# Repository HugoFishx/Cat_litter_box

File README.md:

Cat Litter Box + - Final project of ECE473 @ Umich FA 2021
Group:
    Shiqi Yu
    Haoda Gong
    Yechen Shi
    Ruitao Long
    Tianyang Shi

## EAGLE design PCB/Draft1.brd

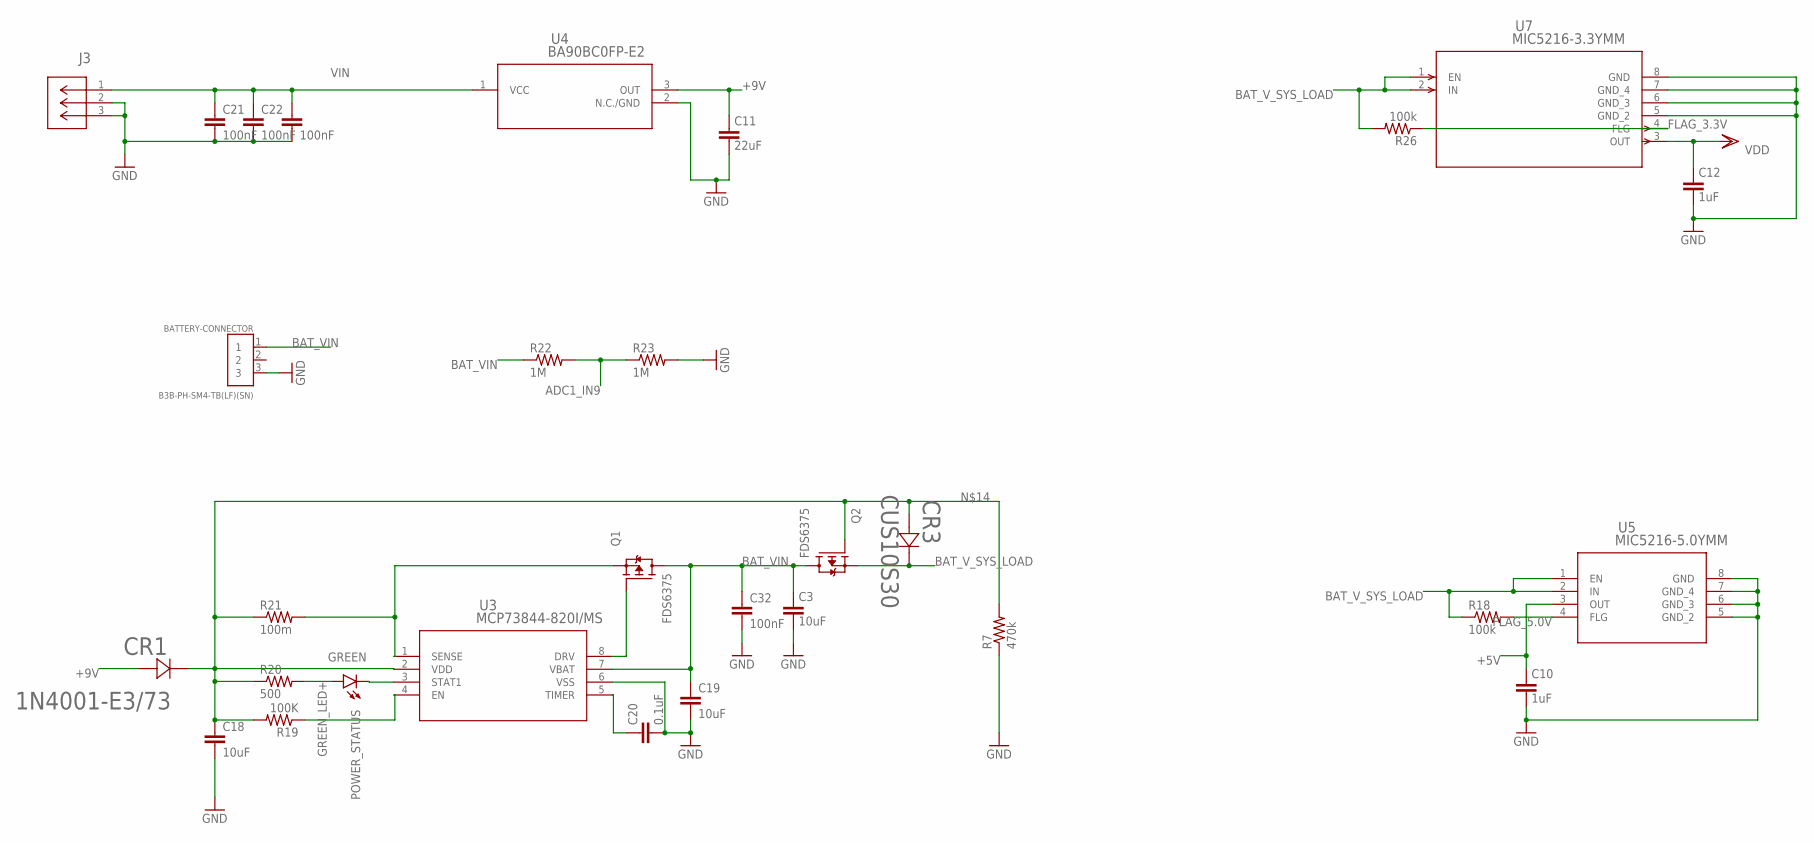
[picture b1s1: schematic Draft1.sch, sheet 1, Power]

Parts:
BATTERY-CONNECTOR: B3B-PH-SM4-TB(LF)(SN); JST_B3B-PH-SM4-TB(LF)(SN)
C3, C18, C19: 10uF; C0603
C10, C12: 1uF; C0603
C11: 22uF; C0603
C20: 0.1uF; C0603
C21, C22, C23, C32: 100nF; C0603
CR1: 1N4001-E3/73; DO-204AL_VIS
CR3: CUS10S30; USC_TOS
J3: EJ503B; CONN_EJ503B_MPD
POWER_STATUS: GREEN; 1206
Q1, Q2: FDS6375; SOIC127P600X175-8N
R7: 470k; R0603
R18, R26: 100k; R0603
R19: 100K; R0603
R20: 500; R0603
R21: 100m; R0603
R22, R23: 1M; R0603
U3: MCP73844-820I/MS; MSOP8_MC_MCH
U4: BA90BC0FP-E2; TO252-3_ROM
U5: MIC5216-5.0YMM; MSOP8_MM_MCH
U7: MIC5216-3.3YMM; MSOP-8_MM_MCL

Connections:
+5V: C10.1, U5.3 (OUT); also elsewhere on the board
+9V: C11.1, CR1.2, U4.3 (OUT)
ADC1_IN9: R22.2, R23.1; also elsewhere on the board
BAT_VIN: BATTERY-CONNECTOR.1, C3.1, C19.1, C32.1, Q1.5 (D), Q1.6 (D), Q1.7 (D), Q1.8 (D), Q2.5 (D), Q2.6 (D), Q2.7 (D), Q2.8 (D), R22.1, U3.7 (VBAT)
BAT_V_SYS_LOAD: CR3.1 (CATHODE), Q2.1 (S), Q2.2 (S), Q2.3 (S), R18.1, R26.2, U5.1 (EN), U5.2 (IN), U7.1 (EN), U7.2 (IN)
FLAG_3.3V: R26.1, U7.4 (FLG)
FLAG_5.0V: R18.2, U5.4 (FLG)
GND: BATTERY-CONNECTOR.3, C3.2, C10.2, C11.2, C12.2, C18.2, C19.2, C20.2, C21.2, C22.2, C23.2, C32.2, J3.2, J3.3, R7.1, R23.2, U3.6 (VSS), U4.2 (N.C./GND), U5.5 (GND_2), U5.6 (GND_3), U5.7 (GND_4), U5.8 (GND), U7.5 (GND_2), U7.6 (GND_3), U7.7 (GND_4), U7.8 (GND); also elsewhere on the board
GREEN_LED+: POWER_STATUS.A, R20.2
unnamed: C18.1, CR1.1, CR3.2 (ANODE), Q2.4 (G), R7.2, R19.2, R20.1, R21.1, U3.2 (VDD)
unnamed: R19.1, U3.4 (EN)
unnamed: POWER_STATUS.C, U3.3 (STAT1)
unnamed: Q1.4 (G), U3.8 (DRV)
unnamed: Q1.1 (S), Q1.2 (S), Q1.3 (S), R21.2, U3.1 (SENSE)
unnamed: C20.1, U3.5 (TIMER)
VDD: C12.1, U7.3 (OUT); also elsewhere on the board
VIN: C21.1, C22.1, C23.1, J3.1, U4.1 (VCC)

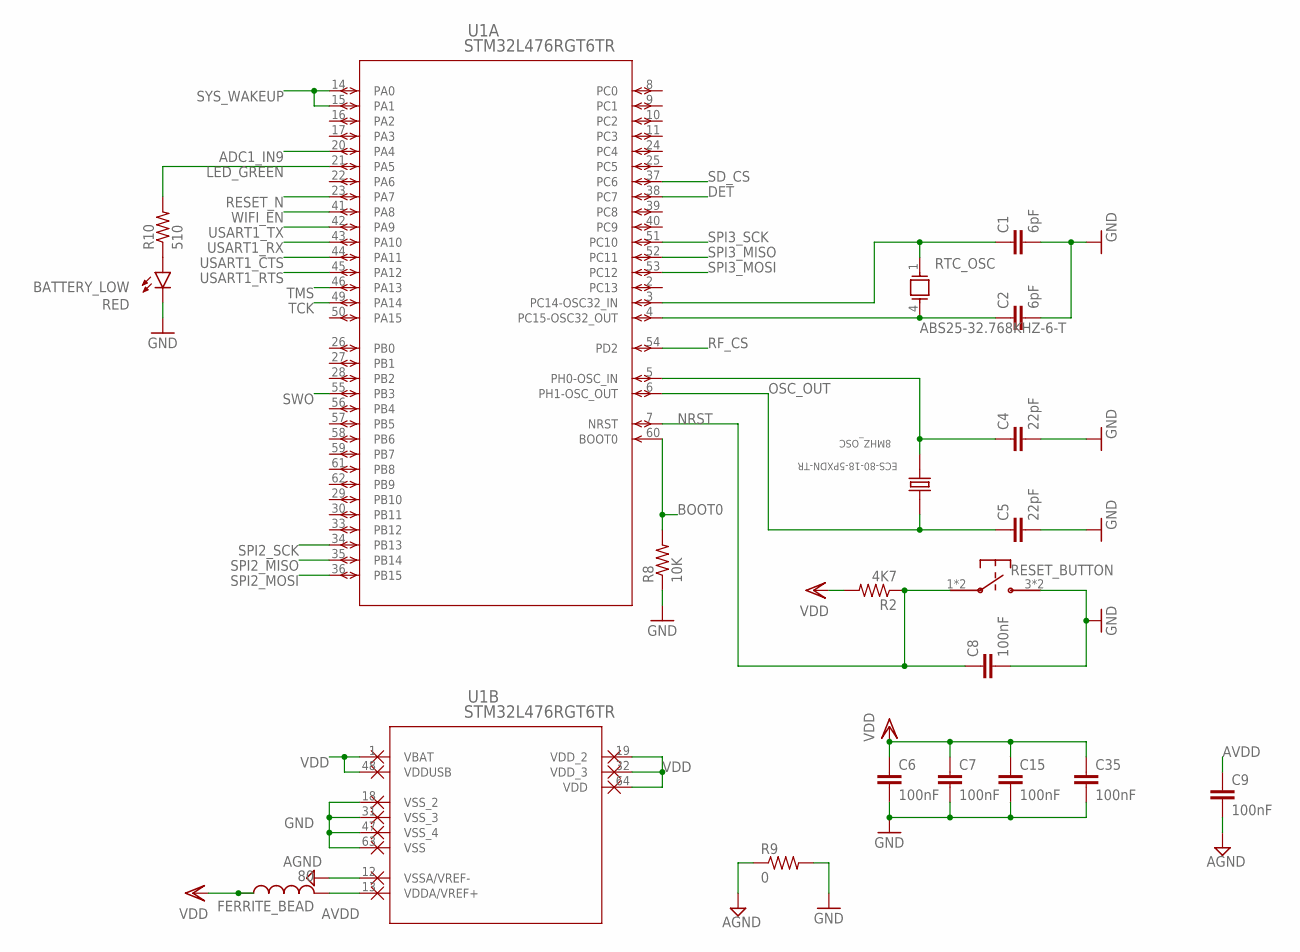
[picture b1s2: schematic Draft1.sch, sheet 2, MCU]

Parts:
8MHZ_OSC: ECS-80-18-5PXDN-TR; XTAL_ECS-80-18-5PXDN-TR
BATTERY_LOW: RED; 1206
C1, C2: 6pF; C0603
C4, C5: 22pF; C0603
C6, C7, C8, C9, C15, C35: 100nF; C0603
FERRITE_BEAD: 80; L3216C
R2: 4K7; R0603
R8: 10K; R0603
R9: 0; R0603
R10: 510; R0603
RESET_BUTTON: PTS645SM43SMTR
RTC_OSC: ABS25-32.768KHZ-6-T; XTAL_ABS25-32.768KHZ-6-T
U1: STM32L476RGT6TR; LQFP64-10X10MM

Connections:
ADC1_IN9: U1.20 (PA4); also elsewhere on the board
AGND: C9.2, R9.1, U1.12 (VSSA/VREF-)
AVDD: C9.1, FERRITE_BEAD.2, U1.13 (VDDA/VREF+)
BOOT0: R8.2, U1.60 (BOOT0)
DET: U1.38 (PC7); also elsewhere on the board
GND: BATTERY_LOW.C, C1.2, C2.2, C4.2, C5.2, C6.2, C7.2, C8.2, C15.2, C35.2, R8.1, R9.2, RESET_BUTTON.3, RESET_BUTTON.4, U1.18 (VSS_2), U1.31 (VSS_3), U1.47 (VSS_4), U1.63 (VSS); also elsewhere on the board
LED_GREEN: R10.2, U1.21 (PA5)
unnamed: BATTERY_LOW.A, R10.1
unnamed: C1.1, RTC_OSC.1, U1.3 (PC14-OSC32_IN)
unnamed: C2.1, RTC_OSC.4, U1.4 (PC15-OSC32_OUT)
NRST: C8.1, R2.1, RESET_BUTTON.1, RESET_BUTTON.2, U1.7 (NRST); also elsewhere on the board
OSC_IN: 8MHZ_OSC.2, C4.1, U1.5 (PH0-OSC_IN)
OSC_OUT: 8MHZ_OSC.1, C5.1, U1.6 (PH1-OSC_OUT); also elsewhere on the board
RESET_N: U1.23 (PA7); also elsewhere on the board
RF_CS: U1.54 (PD2); also elsewhere on the board
SD_CS: U1.37 (PC6); also elsewhere on the board
SPI2_MISO: U1.35 (PB14); also elsewhere on the board
SPI2_MOSI: U1.36 (PB15); also elsewhere on the board
SPI2_SCK: U1.34 (PB13); also elsewhere on the board
SPI3_MISO: U1.52 (PC11); also elsewhere on the board
SPI3_MOSI: U1.53 (PC12); also elsewhere on the board
SPI3_SCK: U1.51 (PC10); also elsewhere on the board
SWO: U1.55 (PB3); also elsewhere on the board
SYS_WAKEUP: U1.14 (PA0), U1.15 (PA1); also elsewhere on the board
TCK: U1.49 (PA14); also elsewhere on the board
TMS: U1.46 (PA13); also elsewhere on the board
USART1_CTS: U1.44 (PA11); also elsewhere on the board
USART1_RTS: U1.45 (PA12); also elsewhere on the board
USART1_RX: U1.43 (PA10); also elsewhere on the board
USART1_TX: U1.42 (PA9); also elsewhere on the board
VDD: C6.1, C7.1, C15.1, C35.1, FERRITE_BEAD.1, R2.2, U1.1 (VBAT), U1.19 (VDD_2), U1.32 (VDD_3), U1.48 (VDDUSB), U1.64 (VDD); also elsewhere on the board
WIFI_EN: U1.41 (PA8); also elsewhere on the board

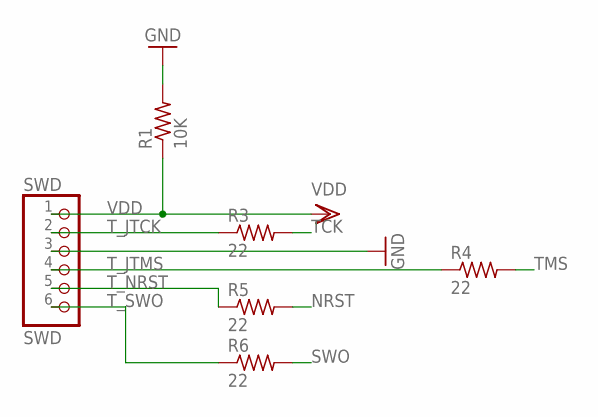
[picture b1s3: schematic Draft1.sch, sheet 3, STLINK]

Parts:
R1: 10K; R0603
R3, R4, R5, R6: 22; R0603
SWD: SWD; 1X06

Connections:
GND: R1.2, SWD.3; also elsewhere on the board
NRST: R5.2; also elsewhere on the board
SWO: R6.2; also elsewhere on the board
TCK: R3.2; also elsewhere on the board
TMS: R4.2; also elsewhere on the board
T_JTCK: R3.1, SWD.2
T_JTMS: R4.1, SWD.4
T_NRST: R5.1, SWD.5
T_SWO: R6.1, SWD.6
VDD: R1.1, SWD.1; also elsewhere on the board

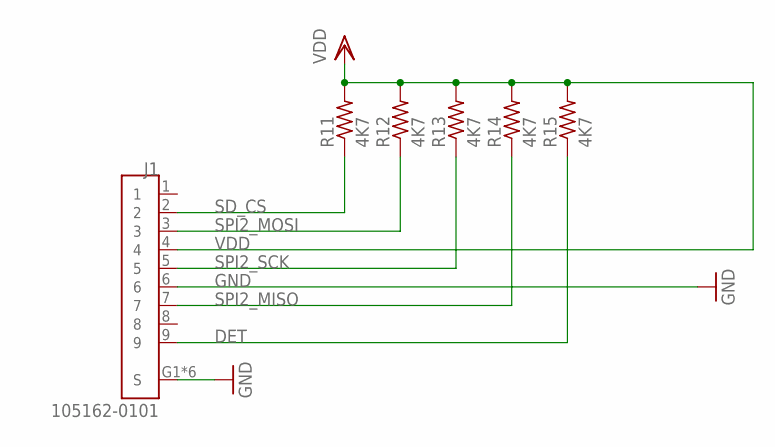
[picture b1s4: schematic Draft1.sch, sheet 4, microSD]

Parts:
J1: 105162-0101; MOLEX_105162-0101
R11, R12, R13, R14, R15: 4K7; R0603

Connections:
DET: J1.9, R15.1; also elsewhere on the board
GND: J1.6, J1.G1 (S), J1.G2 (S), J1.G3 (S), J1.G4 (S), J1.SH1 (S), J1.SH2 (S); also elsewhere on the board
SD_CS: J1.2, R11.1; also elsewhere on the board
SPI2_MISO: J1.7, R14.1; also elsewhere on the board
SPI2_MOSI: J1.3, R12.1; also elsewhere on the board
SPI2_SCK: J1.5, R13.1; also elsewhere on the board
VDD: J1.4, R11.2, R12.2, R13.2, R14.2, R15.2; also elsewhere on the board

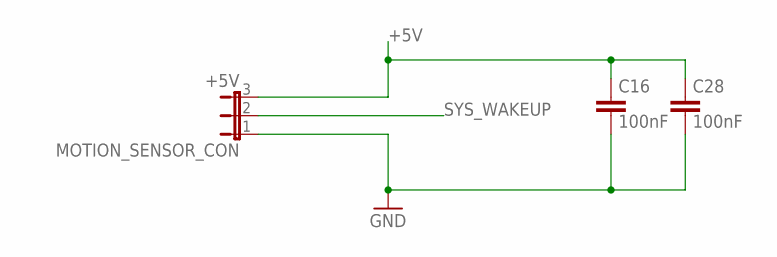
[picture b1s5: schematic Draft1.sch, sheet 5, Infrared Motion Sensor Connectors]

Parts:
C16, C28: 100nF; C0603
MOTION_SENSOR_CON: +5V; JP2

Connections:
+5V: C16.1, C28.1, MOTION_SENSOR_CON.3; also elsewhere on the board
GND: C16.2, C28.2, MOTION_SENSOR_CON.1; also elsewhere on the board
SYS_WAKEUP: MOTION_SENSOR_CON.2; also elsewhere on the board

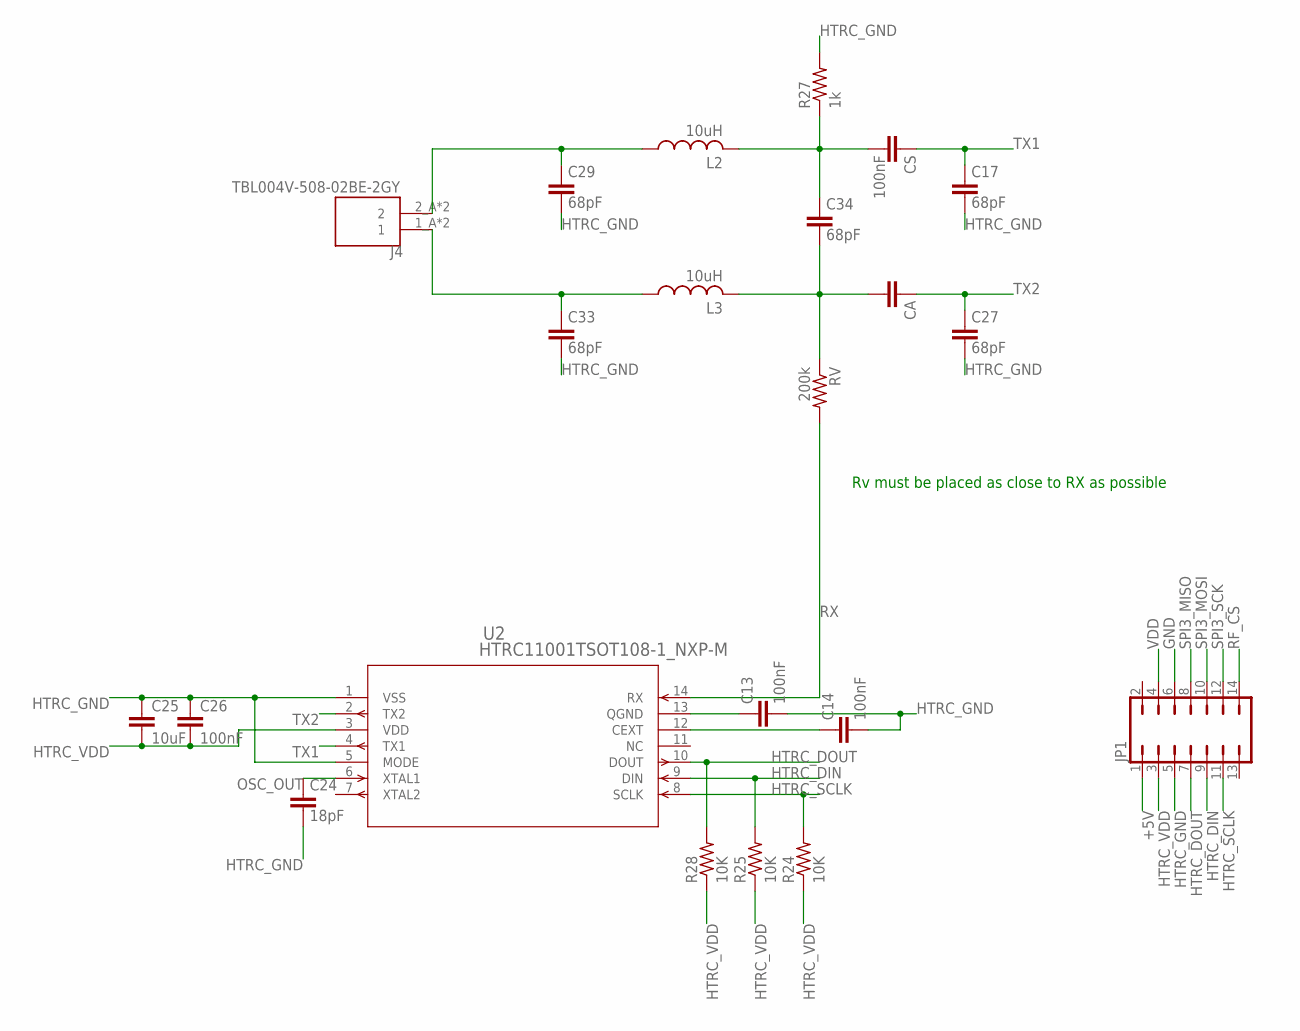
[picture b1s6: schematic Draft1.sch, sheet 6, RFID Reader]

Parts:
C13, C14, C26: 100nF; C0603
C17, C27, C29, C33, C34: 68pF; C0603
C24: 18pF; C0603
C25: 10uF; C0603
CA: C-EUC0603; C0603
CS: 100nF; C0603
J4: TBL004V-508-02BE-2GY; CUI_TBL004V-508-02BE-2GY
JP1: JP7Q
L2, L3: 10uH; L3225M
R24, R25, R28: 10K; R0603
R27: 1k; R0603
RV: 200k; R0603
U2: HTRC11001TSOT108-1_NXP-M; SOT108-1_NXP-M

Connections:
+5V: JP1.1; also elsewhere on the board
GND: JP1.6; also elsewhere on the board
HTRC_DIN: JP1.9, R25.2, U2.9 (DIN)
HTRC_DOUT: JP1.7, R28.2, U2.10 (DOUT)
HTRC_GND: C13.2, C14.2, C17.2, C24.2, C25.1, C26.1, C27.2, C29.2, C33.2, JP1.5, R27.2, U2.1 (VSS), U2.5 (MODE)
HTRC_SCLK: JP1.11, R24.2, U2.8 (SCLK)
HTRC_VDD: C25.2, C26.2, JP1.3, R24.1, R25.1, R28.1, U2.3 (VDD)
unnamed: C33.1, J4.1_A (1), J4.1_B (1), L3.1
unnamed: C29.1, J4.2_A (2), J4.2_B (2), L2.1
unnamed: C34.1, CS.2, L2.2, R27.1
unnamed: C13.1, U2.13 (QGND)
unnamed: C34.2, CA.2, L3.2, RV.1
unnamed: C14.1, U2.12 (CEXT)
OSC_OUT: C24.1, U2.6 (XTAL1); also elsewhere on the board
RF_CS: JP1.14; also elsewhere on the board
RX: RV.2, U2.14 (RX)
SPI3_MISO: JP1.8; also elsewhere on the board
SPI3_MOSI: JP1.10; also elsewhere on the board
SPI3_SCK: JP1.12; also elsewhere on the board
TX1: C17.1, CS.1, U2.4 (TX1)
TX2: C27.1, CA.1, U2.2 (TX2)
VDD: JP1.4; also elsewhere on the board

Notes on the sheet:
Rv must be placed as close to RX as possible

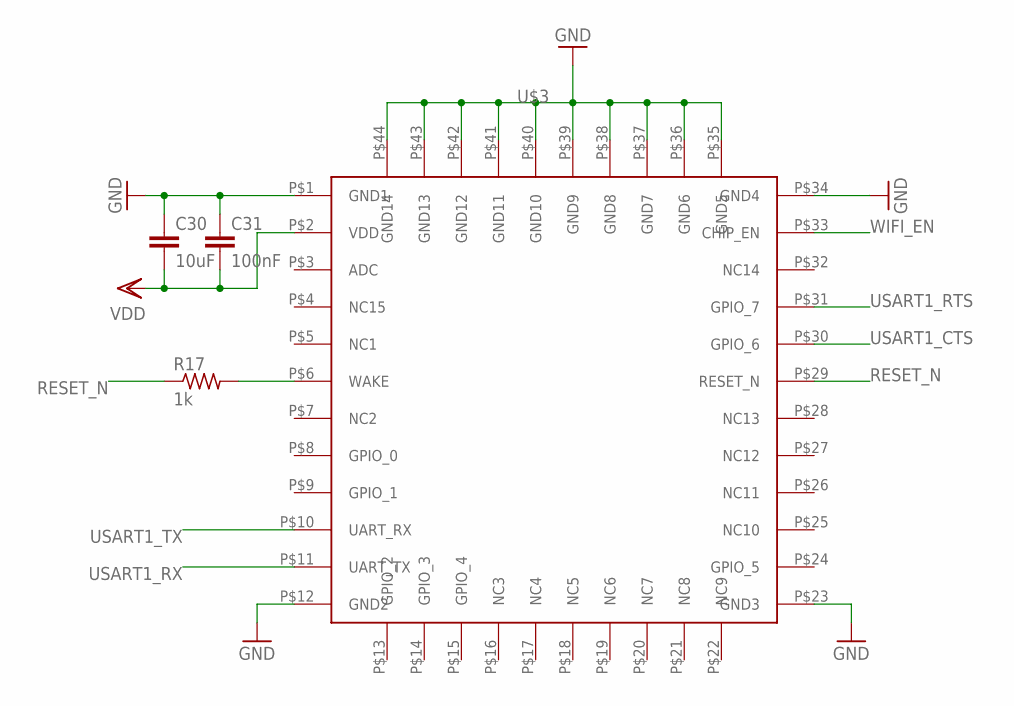
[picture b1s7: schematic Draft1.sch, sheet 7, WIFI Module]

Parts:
C30: 10uF; C0603
C31: 100nF; C0603
R17: 1k; R0603
U$3: AMW037-2.2.14R

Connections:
GND: C30.1, C31.1, U$3.P$1 (GND1), U$3.P$12 (GND2), U$3.P$23 (GND3), U$3.P$34 (GND4), U$3.P$35 (GND5), U$3.P$36 (GND6), U$3.P$37 (GND7), U$3.P$38 (GND8), U$3.P$39 (GND9), U$3.P$40 (GND10), U$3.P$41 (GND11), U$3.P$42 (GND12), U$3.P$43 (GND13), U$3.P$44 (GND14); also elsewhere on the board
unnamed: R17.2, U$3.P$6 (WAKE)
RESET_N: R17.1, U$3.P$29 (RESET_N); also elsewhere on the board
USART1_CTS: U$3.P$30 (GPIO_6); also elsewhere on the board
USART1_RTS: U$3.P$31 (GPIO_7); also elsewhere on the board
USART1_RX: U$3.P$11 (UART_TX); also elsewhere on the board
USART1_TX: U$3.P$10 (UART_RX); also elsewhere on the board
VDD: C30.2, C31.2, U$3.P$2 (VDD); also elsewhere on the board
WIFI_EN: U$3.P$33 (CHIP_EN); also elsewhere on the board

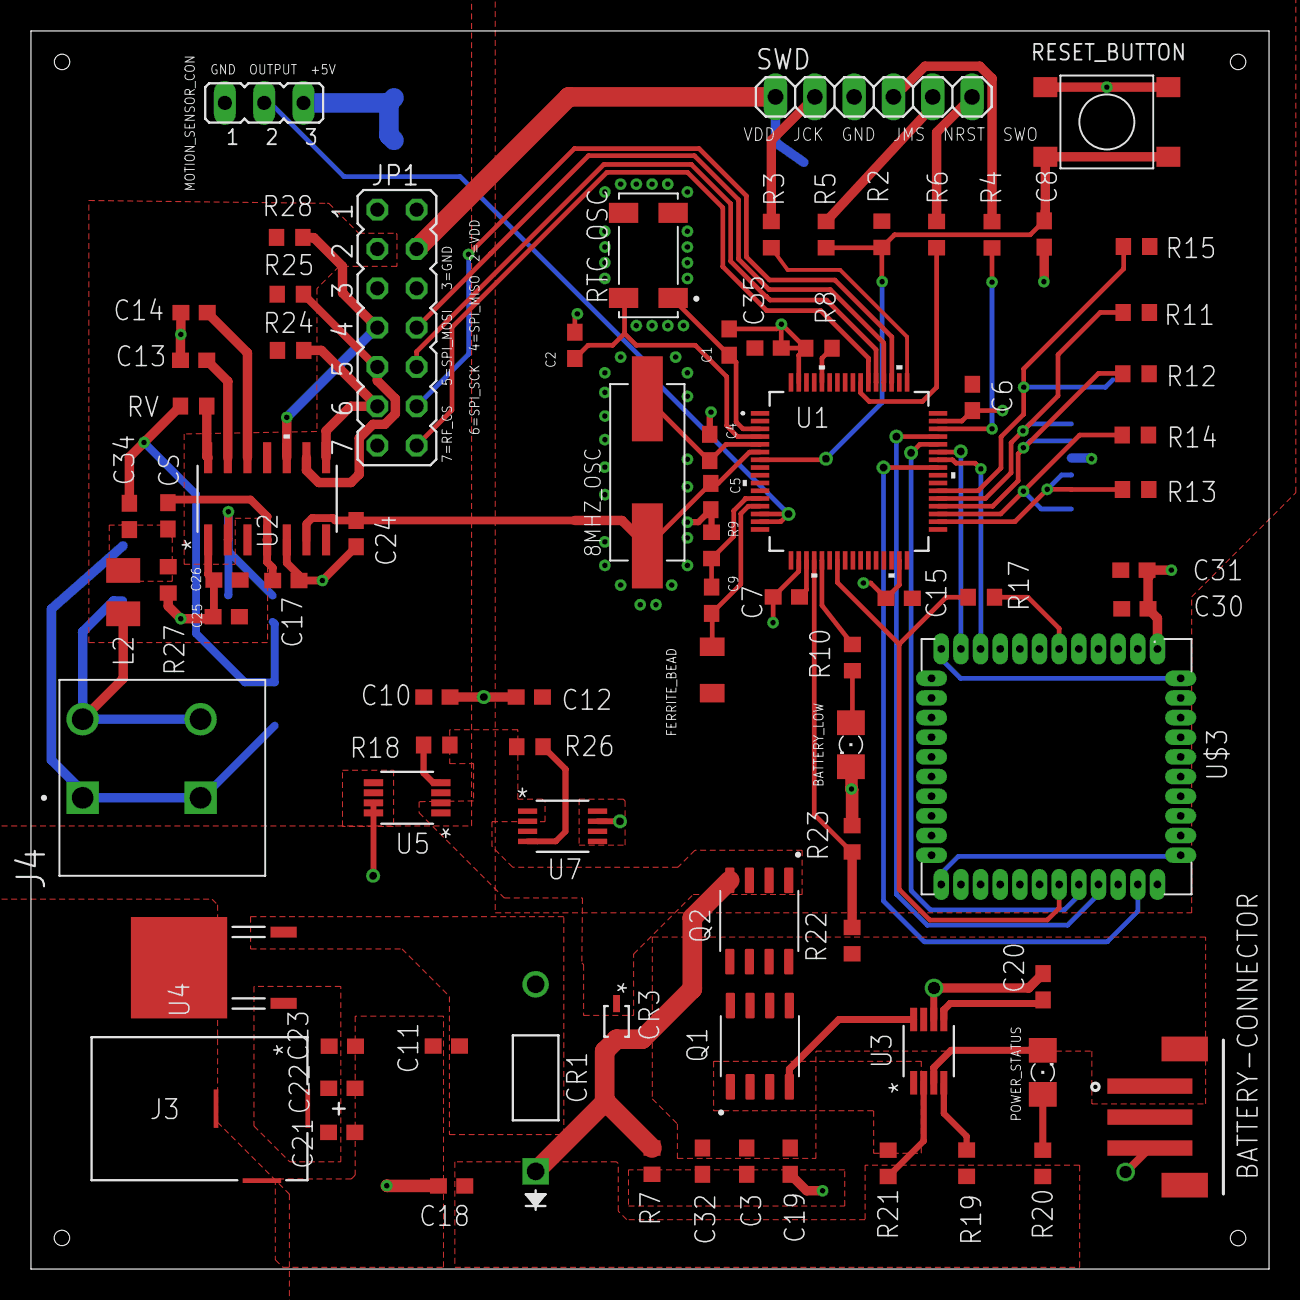
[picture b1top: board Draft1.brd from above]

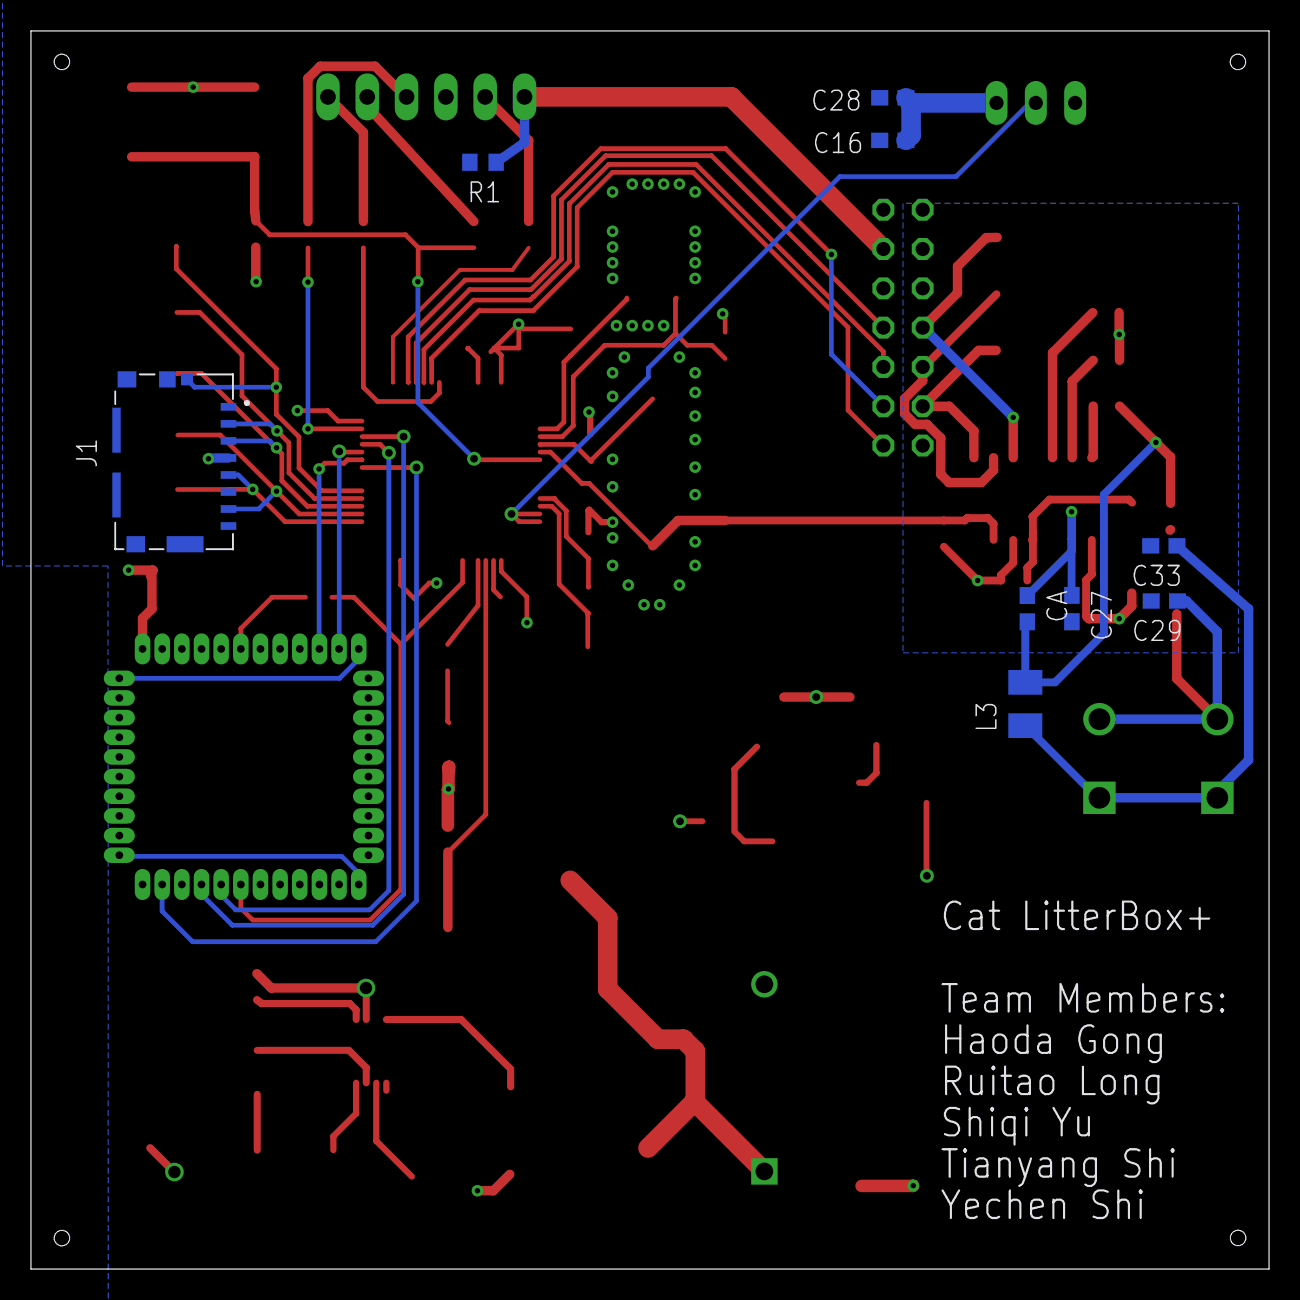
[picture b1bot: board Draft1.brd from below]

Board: 2 copper layers, 80.0 x 80.0 mm, 91 parts (9 on the bottom side), 65 nets.

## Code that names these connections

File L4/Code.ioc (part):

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Mcu.Name=STM32L476R(C-E-G)Tx
Mcu.Package=LQFP64
Mcu.UserName=STM32L476RGTx
PA0.Mode=SYS_WakeUp0
PA0.Signal=SYS_WKUP1
PA1.GPIOParameters=GPIO_Label,GPIO_ModeDefaultEXTI
PA1.GPIO_Label=MOTION_SENSOR_PIN
PA1.GPIO_ModeDefaultEXTI=GPIO_MODE_IT_RISING_FALLING
PA1.Signal=GPXTI1
PA10.Mode=Asynchronous
PA10.Signal=USART1_RX
PA13\ (JTMS-SWDIO).GPIOParameters=GPIO_Label
PA13\ (JTMS-SWDIO).GPIO_Label=TMS
PA13\ (JTMS-SWDIO).Mode=Serial_Wire
PA13\ (JTMS-SWDIO).Signal=SYS_JTMS-SWDIO
PA14\ (JTCK-SWCLK).GPIOParameters=GPIO_Label
PA14\ (JTCK-SWCLK).GPIO_Label=TCK
PA14\ (JTCK-SWCLK).Mode=Serial_Wire
PA14\ (JTCK-SWCLK).Signal=SYS_JTCK-SWCLK
PA2.Mode=Asynchronous
PA2.Signal=USART2_TX
PA3.GPIOParameters=GPIO_Speed,GPIO_PuPd,GPIO_Label,GPIO_Mode
PA3.GPIO_Label=USART_RX
PA3.GPIO_Mode=GPIO_MODE_AF_PP
PA3.GPIO_PuPd=GPIO_NOPULL
PA3.GPIO_Speed=GPIO_SPEED_FREQ_VERY_HIGH
PA3.Mode=Asynchronous
PA3.Signal=USART2_RX
PA4.Signal=SharedAnalog_PA4
PA5.GPIOParameters=GPIO_Label
PA5.GPIO_Label=BATTERY_LOW_LED
PA5.Signal=GPIO_Output
PA7.GPIOParameters=GPIO_Label
PA7.GPIO_Label=WIFI_RESET
PA7.Signal=GPIO_Output
PA8.GPIOParameters=GPIO_Label
PA8.GPIO_Label=WIFI_EN
PA8.Signal=GPIO_Output
PA9.Mode=Asynchronous
PA9.Signal=USART1_TX
PB13.Mode=Full_Duplex_Master
PB13.Signal=SPI2_SCK
PB14.Mode=Full_Duplex_Master
PB14.Signal=SPI2_MISO
PB15.Mode=Full_Duplex_Master
PB15.Signal=SPI2_MOSI
PB3\ (JTDO-TRACESWO).GPIOParameters=GPIO_Label
PB3\ (JTDO-TRACESWO).GPIO_Label=SWO
PB3\ (JTDO-TRACESWO).Signal=SYS_JTDO-SWO
PC10.Mode=Full_Duplex_Master
PC10.Signal=SPI3_SCK
PC11.Mode=Full_Duplex_Master
PC11.Signal=SPI3_MISO
PC12.Mode=Full_Duplex_Master
PC12.Signal=SPI3_MOSI
PC13.GPIOParameters=GPIO_PuPd,GPIO_Label,GPIO_ModeDefaultEXTI
PC13.GPIO_Label=B1 [Blue PushButton]
PC13.GPIO_ModeDefaultEXTI=GPIO_MODE_IT_FALLING
PC13.GPIO_PuPd=GPIO_NOPULL
PC13.Signal=GPXTI13
PC14-OSC32_IN\ (PC14).Signal=RCC_OSC32_IN
PC15-OSC32_OUT\ (PC15).Signal=RCC_OSC32_OUT
PC4.Mode=Asynchronous
PC4.Signal=USART3_TX
PC5.Mode=Asynchronous
PC5.Signal=USART3_RX
PC6.GPIOParameters=GPIO_Label
PC6.GPIO_Label=MICROSD_CS
PC6.Signal=GPIO_Output
PC7.GPIOParameters=GPIO_Label
PC7.GPIO_Label=MICROSD_DET
PC7.Signal=GPIO_Input
PD2.GPIOParameters=GPIO_Label
PD2.GPIO_Label=RFID_CS
PD2.Signal=GPIO_Output
PH0-OSC_IN\ (PH0).Mode=HSE-External-Oscillator
PH0-OSC_IN\ (PH0).Signal=RCC_OSC_IN
PH1-OSC_OUT\ (PH1).Mode=HSE-External-Oscillator
PH1-OSC_OUT\ (PH1).Signal=RCC_OSC_OUT
RCC.HSE_VALUE=8000000
RCC.SYSCLKFreq_VALUE=10000000
RCC.SYSCLKSource=RCC_SYSCLKSOURCE_PLLCLK
board=NUCLEO-L476RG
boardIOC=true

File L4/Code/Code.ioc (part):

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Mcu.Name=STM32L476R(C-E-G)Tx
Mcu.Package=LQFP64
Mcu.UserName=STM32L476RGTx
PA0.GPIOParameters=GPIO_Label
PA0.GPIO_Label=MS
PA0.Signal=GPXTI0
PA10.Mode=Asynchronous
PA10.Signal=USART1_RX
PA11.Mode=CTS_RTS
PA11.Signal=USART1_CTS
PA12.Mode=CTS_RTS
PA12.Signal=USART1_RTS
PA13\ (JTMS-SWDIO).GPIOParameters=GPIO_Label
PA13\ (JTMS-SWDIO).GPIO_Label=TMS
PA13\ (JTMS-SWDIO).Mode=Serial_Wire
PA13\ (JTMS-SWDIO).Signal=SYS_JTMS-SWDIO
PA14\ (JTCK-SWCLK).GPIOParameters=GPIO_Label
PA14\ (JTCK-SWCLK).GPIO_Label=TCK
PA14\ (JTCK-SWCLK).Mode=Serial_Wire
PA14\ (JTCK-SWCLK).Signal=SYS_JTCK-SWCLK
PA2.GPIOParameters=GPIO_Speed,GPIO_PuPd,GPIO_Label,GPIO_Mode
PA2.GPIO_Label=USART_TX
PA2.GPIO_Mode=GPIO_MODE_AF_PP
PA2.GPIO_PuPd=GPIO_NOPULL
PA2.GPIO_Speed=GPIO_SPEED_FREQ_VERY_HIGH
PA2.Mode=Asynchronous
PA2.Signal=USART2_TX
PA3.GPIOParameters=GPIO_Speed,GPIO_PuPd,GPIO_Label,GPIO_Mode
PA3.GPIO_Label=USART_RX
PA3.GPIO_Mode=GPIO_MODE_AF_PP
PA3.GPIO_PuPd=GPIO_NOPULL
PA3.GPIO_Speed=GPIO_SPEED_FREQ_VERY_HIGH
PA3.Mode=Asynchronous
PA3.Signal=USART2_RX
PA5.GPIOParameters=GPIO_Label
PA5.GPIO_Label=BATTERY_LOW_LED
PA5.Signal=GPIO_Output
PA8.GPIOParameters=GPIO_Label
PA8.GPIO_Label=WIFI_EN
PA8.Signal=GPIO_Output
PA9.Mode=Asynchronous
PA9.Signal=USART1_TX
PB10.Mode=Full_Duplex_Master
PB10.Signal=SPI2_SCK
PB13.GPIOParameters=GPIO_Label
PB13.GPIO_Label=CS_SD
PB13.Signal=GPIO_Output
PB14.GPIOParameters=GPIO_Label
PB14.GPIO_Label=DET
PB14.Signal=GPIO_Input
PB3\ (JTDO-TRACESWO).GPIOParameters=GPIO_Label
PB3\ (JTDO-TRACESWO).GPIO_Label=SWO
PB3\ (JTDO-TRACESWO).Signal=SYS_JTDO-SWO
PC0.Signal=ADCx_IN1
PC10.Mode=Full_Duplex_Master
PC10.Signal=SPI3_SCK
PC11.Mode=Full_Duplex_Master
PC11.Signal=SPI3_MISO
PC12.Mode=Full_Duplex_Master
PC12.Signal=SPI3_MOSI
PC13.GPIOParameters=GPIO_PuPd,GPIO_Label,GPIO_ModeDefaultEXTI
PC13.GPIO_Label=B1 [Blue PushButton]
PC13.GPIO_ModeDefaultEXTI=GPIO_MODE_IT_FALLING
PC13.GPIO_PuPd=GPIO_NOPULL
PC13.Signal=GPXTI13
PC14-OSC32_IN\ (PC14).Mode=LSE-External-Oscillator
PC14-OSC32_IN\ (PC14).Signal=RCC_OSC32_IN
PC15-OSC32_OUT\ (PC15).Mode=LSE-External-Oscillator
PC15-OSC32_OUT\ (PC15).Signal=RCC_OSC32_OUT
PC2.Mode=Full_Duplex_Master
PC2.Signal=SPI2_MISO
PC3.Mode=Full_Duplex_Master
PC3.Signal=SPI2_MOSI
PH0-OSC_IN\ (PH0).Mode=HSE-External-Oscillator
PH0-OSC_IN\ (PH0).Signal=RCC_OSC_IN
PH1-OSC_OUT\ (PH1).Mode=HSE-External-Oscillator
PH1-OSC_OUT\ (PH1).Signal=RCC_OSC_OUT
RCC.HSE_VALUE=8000000
RCC.SYSCLKFreq_VALUE=80000000
RCC.SYSCLKSource=RCC_SYSCLKSOURCE_PLLCLK
board=NUCLEO-L476RG
boardIOC=true

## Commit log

2021-10-07 Setup
2021-10-11 Arduino prototype framework
2021-10-12 Arduino motion sensor handler
2021-10-12 resource doc
2021-10-12 wrap up motion sensor
2021-10-12 ESP32 setup & serial communication & UDP
2021-10-12 weird bug in UDP
    UDP not correct when there are more than 11 bytes in the packet
2021-10-13 SD card integrated & cmd via serial
2021-10-13 trivial
2021-10-14 Arduino Low Power
2021-10-14 125kHz low freq RFID, able to extract tags
2021-10-14 Web Server & UDP fixed & buglog
2021-10-14 Have to put Arduino file in folder with same name
2021-10-15 RFID reader integrated & box->server enabled
    Type "Send" in terminal monitor of Arduino -> Everything in txt will be sent to WiFi via serial -> WiFi send everything to server via UDP -> server shows
2021-10-15 code cleanup & comment
2021-10-17 RFID High Freq, looking for capable tags now
2021-10-17 Update RFID_HF.ino
    Additional comment
2021-10-18 Serial not working
2021-10-18 Demo version
2021-10-27 STM32L4 template
2021-10-27 STM32 global var
2021-10-27 IDE misc.
2021-10-28 Create L0
2021-10-28 Create Code
2021-10-28 Create 1
2021-10-28 settings
2021-10-28 Create m
2021-10-28 Create 2
2021-10-28 Revert "Add files via upload"
    This reverts commit 919975b84332fd9229dee4e8f3777e6d0fce7f2d.
2021-10-28 Revert "Add files via upload"
    This reverts commit 968ace8c966d6980c719b7c46ae1b69014c17666.
2021-10-28 Revert "Delete 2"
    This reverts commit 5c285e8d4458aaac7cd09be0cc643f100cf6bf6f.
2021-10-28 Revert "Add files via upload"
    This reverts commit 1cbe18323d0a6cdc5d3568ccc157ae3d16499e68.
2021-10-28 Revert "Delete 1"
    This reverts commit 527cac68189afba9246e0edb16512f9e918f9854.
2021-10-28 Revert "Create 2"
    This reverts commit 81a8b671b68139bf5a32da8fa640331fce31f863.
2021-10-28 Revert "Create 1"
    This reverts commit 0194ef24cc6501a5a42415a4d76d86bc21271794.
2021-10-28 Revert "Delete m"
    This reverts commit 6d71d60d2e7ac5be4feda9c538478ded06a12e54.
2021-10-28 Revert "Delete 1"
    This reverts commit 02c8c35720886de05cb12ade2e9305d5f6f16577.
2021-10-28 Revert "Add files via upload"
    This reverts commit ce9009c5bf4e3604697362afc9aa52369cee98c2.
2021-10-28 Revert "Create 1"
    This reverts commit 4f25d6222882119fd56042145e861587932947ec.
2021-10-28 Revert "Delete 1"
    This reverts commit 8097938a198f475cbffbf91f3b46e288075b9b44.
2021-10-28 Revert "Add files via upload"
    This reverts commit fbd02aaed7ea56a60dacf479b788d6d211fb39fc.
2021-10-28 Revert "Create 1"
    This reverts commit 6d5976e924c3e23e2f7087086eac4bc960ecd1d4.
2021-10-28 Revert "Delete 1"
    This reverts commit bdd442f437d817b50b89deb0689208c96d54126d.
2021-10-28 Revert "Add files via upload"
    This reverts commit d089e50e1edb4b0ad72dabe849cc619d178d462c.
2021-10-28 Revert "Create m"
    This reverts commit c31f5e4a6d235347f6c2d7db0575254099329251.
2021-10-28 Revert "Add files via upload"
    This reverts commit abf1060aa0694c87d526d7e246e048186f4a42fe.
2021-10-28 Revert "Create 1"
    This reverts commit 04cfc3c71bf124204b2a83d95af008f503044d07.
2021-10-28 Revert "Delete 1"
    This reverts commit 65c83b016acf5fe2c49363f25b53912a3fda26c2.
2021-10-28 Revert "Delete 1"
    This reverts commit 06029298838603dcb34d552deded93255395e750.
2021-10-28 Revert "Add files via upload"
    This reverts commit d0a4fe483bc3a3c76e1d781c8829ade70840abd8.
2021-10-28 Revert "settings"
    This reverts commit fca2396a4754a820cfc241ff0f387c486dd4d344.
2021-10-28 Revert "IDE misc."
    This reverts commit 92b3a48b9c3ea49db8cfff98d12b8510fe5fddb4.
2021-10-28 Revert "Delete L0 directory"
    This reverts commit f413a5eeb727ea661af1fe393f26175328d57024.
2021-10-28 Revert "Create 1"
    This reverts commit 64f306973a750298d6b5f0f8dd761d90af666684.
2021-10-28 Revert "Create 1"
    This reverts commit 5bca80d732536a750ee5e3fe1910a0928b2d10fe.
2021-10-28 Revert "Delete L0/Code/.settings directory"
    This reverts commit 27dfe8b3d4b908a284c2bc42e763b90e729ad130.
2021-10-28 Revert "Add files via upload"
    This reverts commit c65b166487e682419a6686bb84ea2639218b9824.
2021-10-28 Revert "Create 1"
    This reverts commit 637419451e21cd36dd28999d0638e9d9d7cca79f.
2021-10-28 Revert "Delete L0 directory"
    This reverts commit 08ef9a91fe60aa3e1986ad4168966514f55c389c.
2021-10-28 Revert "Add files via upload"
    This reverts commit e25273d6d498b66505e2bdc81bd56d03a710f7ec.
2021-10-28 Revert "Create Code"
    This reverts commit 8929a1749ed06db5f215db95330fbcf2c7419a55.
2021-10-28 Revert "Delete L0"
    This reverts commit cfc80746de107640ca679f5d89c8d308e7afe6ff.
2021-10-28 Revert "Create L0"
    This reverts commit 980ef14f285316ff1258c34aed6fee62c5bea29a.
2021-10-28 Revert "Update .gitignore"
    This reverts commit 7183ca65373adacdb4219109a9ae8c3cd135edc9.
2021-10-28 Revert "Update .gitignore"
    This reverts commit 5bd263f6ce67994b0a69955aa8a3a4081cf3728e.
2021-10-28 Revert "IDE misc."
    This reverts commit 3cc6d9edf36aeb11f69b9db22a9ecda66d3617ec.
2021-10-28 Revert "STM32 global var"
    This reverts commit 98be9cbf0f283b3a777feb53e50c74585a7911fe.
2021-10-28 Revert "STM32L4 template"
    This reverts commit ddf51d05eda42d09f79252aeee1102c711c99dcc.
2021-10-28 STM32CubeIDE init L4
2021-10-28 .gitignore
2021-10-28 Enable PA9 as interrupt pin
2021-10-28 Interrupt
2021-10-29 Waiting for serial
2021-10-29 STM32L0 SPI+SDcard test(unfinished)
2021-10-29 SD card lib
    Change include in sdcard.h to match the board
2021-10-29 FatFs configured
2021-10-29 SD card test from tutorial
    Pin & Serial configuration needed
2021-10-29 Configure SPI for SD card
2021-10-31 SDcard test case + uart5 debug
    Revert "Create 1"
2021-11-10 this is a test for vscode. no change to source code
2021-11-10 Get request forward done
2021-11-11 SDcard write + GPIO interrupt event
2021-11-12 Motion-triggered SDcard writing event + wifi
2021-11-13 SDcard+motion sensor+wifi
2021-11-14 local server
2021-11-14 Wifi_write_event modified
2021-11-14 Revert "Wifi_write_event modified"
    This reverts commit d7a61881acb64a221bb634faf461db6433fc1ccc.
2021-11-15 RFID+Motion+SDcard+Wifi(pending verification)
2021-11-20 MS2 demo
2021-11-20 Reselect pinouts for STM32L476RG
2021-11-20 pinout/location/battery sesning changes
2021-11-21 + low power sleep mode (standby mode abandoned, so PA0 needs to be disabled in MX)
2021-11-25 Test with PCB, HSE working correctly, LSE (RTC) not working
2021-11-29 MS2demo transplanted on PCB
2021-12-09 one night before expo
2021-12-10 Expo version

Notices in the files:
parts and their libraries:
COPYRIGHT: Copyright (C) 2021 Ultra Librarian. All rights reserved.
